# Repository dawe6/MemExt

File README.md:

# MemExt
## Obsah
    • Úvod 
    • Realizace zapojení 
        ◦ Popis zapojení 
        ◦ Instalace modulu 
    • Používání modulu MemExt 
        ◦ Příklady nastavení stránkování 
        ◦ Inicializace stránkování 
        ◦ Postup při programování FLASH 
        ◦ Programování FLASH mimo MZ800 
        ◦ Obsah paměti FLASH 

## Úvod
Modul MemExt umožní používat v MZ800 až 1 MB operační paměti. Obsahuje stránkovací systém, který převádí 16-ti bitovou adresu mikroprocesoru Z80 na 20-ti bitovou adresu paměti. 
      Slovníček pojmů:
    • Logická paměť - to je paměť kterou známe jako fyzickou RAM z MZ800 před instalací MemExt. Má velikost 64kB a může mít adresu 0-FFFFh. 
    • Fyzická paměť - to je celková paměť. Její velikost je 1MB a může mít adresu 0-FFFFFh. Je rozdělená na dvě části 512 kB RAM a 512 kB FLASH. 
    • Stránkovací paměť - je prostředníkem mezi logickou a fyzickou pamětí. Její velikost je pouhých 16 bajtů. 
    • Stránkování - je hlavní činností modulu MemExt. Je to převod 16-ti bitové adresy na 20-ti bitovou. Ve skutečnosti ovšem nejvyšší 4 adresní bity (A12-A15) adresují jednu z 16-ti buněk stránkovací paměti a její 8-mi bitový výstup pak doplní 12 nižších adresních bitů (A0-A11) na 20-ti bitovou adresu. 
    • Stránkovací adresa - má tento tvar "BB:AAA" kde BB /0-FFh/ je obsah stránkovací paměti, "AAA" /0-FFFh/ jsou spodní nestránkované bity adresy. 
    • Stránka - má velikost 4 kB. Logická paměť má 16 stránek, fyzická paměť pak 256 z toho 128 v RAM a 128 ve FLASH. 
    • Mapování - je mapování pamětí VRAM a PROM pomocí I/O portů 0E0h-0E4h. Mapování je nadřazeno stránkování. Pokud přimapujeme část FLASH budu ji označovat jako PROM, protože do mapované FLASH není možný zápis. Pro programování FLASH je nutné použít stránkování. MemExt rozšiřuje vlastnosti mapování PROM na možnost volit ze dvou 16 kB části FLASH přepínačem MZ700/MZ800. 
Nastavení stránkovací paměti se provádí zápisem na I/O port E7h, kde se 8 bitů datové sběrnice zapisuje do buňky určené nejvyššími 4-mi bity 16-ti bitové adresní sběrnice, nastavení tedy musí být provedeno instrukcí OUT (C), r kdy vyšší 4 bity registru B určují adresu ve stránkovací paměti. Zapojení neumožňuje stránkovací paměť programově číst. 

## Popis zapojení
    • Adresní dekodér I/O portu E7h - Je tvořen obvody LS138 a LS10 (3 hradla).
Výstupem je pin 15 obvodu LS138 a nabývá log "0" při zápisu do I/O portu E7h. 
    • Logika módu stránkování / mapování - Sestává pouze z obvodu LS157.
Vstupem S (pin 1 LS157) je signál /CSROM (původní /CS pro paměť PROM). Mux s výstupem Q3 (pin 9) funguje jako invertor signálu /CSROM a jeho aktivita zakazuje stránkovací paměť a generuje signál /CS pro paměť FLASH. Pokud je vstup /CSROM aktivní (log "0") platí:
- signál /ME (memory enabled) u obvodů 7489 je v log "1",
- signál /CS u paměti FLASH je v log "0",
- B12 = A12 (mux s výstupem Q1 pin 4),
- B13 = A13 (mux s výstupem Q4 pin 12),
- B14, B15 = log "0" (výstupy stránkovací paměti v log "1" a invertor),
- B16 = stav přepínače, mód MZ700 = log "1", mód MZ800 = log "0", (mux s výstupem Q2 pin 7),
- B17, B18 = log "1" (výstupy stránkovací paměti v log "1"). 
    • Stránkovací paměť - Je tvořen dvěma obvody 7489, pěti invertory obvodu LS04, osmi odpory 1k (obvod 7489 má na výstupu otevřený kolektor)
Paměť je neaktivní jedině v případě aktivity signálu /CSROM (mód mapování). Jinak paměť neustále generuje podle bitů A12 - A15 adresní sběrnice signály B12 - B19. V případě zápisu do I/O portu E7h je aktivní signál /WE (pin 3) a bity datové sbětnice se zapíší do buňky stránkovací paměti vybrané bity A12 - A15 adresní sběrnice 
    • Logika výběru RAM / FLASH - Sestává z obvodu LS02 (4 hradla) a invertoru obvodu LS04.
Vstupem je signál /CAS, který aktivoval původní paměťové čipy 4164 - nyní vstupuje na piny 6 a 8 obvodu LS02. Druhým rozhodovacím signálem je nejvyšší adresní výstup stránkovací paměti B19 - ten rozhodne zda bude aktivována paměť RAM nebo FLASH. Paměť FLASH může být také aktivovaná signálem /CSROM. 
    • Paměti FLASH/RAM - Obvody 29F040 a 628512.
Tady snad jedině že 628512 nemá uspořádané piny jako 29F040 tak jsou adresní vodiče v zapojení poněkud přeházené, ale vzhledem k tomu že je to RAM tak to snad ani nevadí. 

## Instalace modulu
    • Nejprve je třeba si připravit pomocný datový konektor se sedmi vodiči a připájet je podle obrázku mb.jpg na základní desku. Pořadí vodičů na pomocném konektoru (od zadní části MZ800) je:
A14
/WR
/RD
/IORQ
A15
7/8
/CAS. 
    • Druhým krokem je odstavení stávajících čipů RAM 4164. To je realizováno přerušením signálu CAS. Podle obrázku mb.jpg najděte nad obvodem 8253 čtyři odpory v řadě (na mém obrázku je čtvrtý odpor nahrazen propojkou, kterou jsem tam dal kvůli testování abych nemusel stále pájet). Vypájejte nožičku čtvrtého odporu směřující k obvodu 74LS125 a připojte ji na +5V. 
    • Teď vyndejte z patice paměť PROM a místo ní vložte modul a připojte pomocný datový konektor. 
    • Mužete zkusit co to udělá, když se to zapne. 

## Příklady nastavení stránkování
Ovládání stránkovacího mechanizmu je velice jednoduché tak jen pár příkladů: 
      Ať logickou paměť 2000-2FFF tvoří stránka 00 (první stránka RAM) 
    • LD BC, 20E7 - B=adresa stránkovací paměti 2, C=port stránkování 
    • LD A, 00 - A=stránka 
    • OUT (C), A
Ať logickou paměť 9000-9FFF tvoří stránka 7F (poslední stránka RAM) 
    • LD BC, 90E7 - B=adresa stránkovací paměti 9, C=port stránkování 
    • LD A, 7F - A=stránka 
    • OUT (C), A
Ať logickou paměť 4000-4FFF tvoří stránka 80 (první stránka FLASH) 
    • LD BC, 40E7 - B=adresa stránkovací paměti 4, C=port stránkování 
    • LD A, 80 - A=stránka 
    • OUT (C), A
Ať logickou paměť C000-CFFF tvoří stránka FF (poslední stránka FLASH) 
    • LD BC, C0E7 - B=adresa stránkovací paměti C, C=port stránkování 
    • LD A, FF - A=stránka 
    • OUT (C), A
Představme si, že máme odmapované všechny PROM a SHARP je v módu MZ-800 a chceme pomocí stránkování provést ekvivalent příkazu OUT (E4), A. 
    • LD BC, 00E7 - B=adresa stránkovací paměti 0, C=port stránkování 
    • LD A, 80 - A=stránka 
    • OUT (C), A 
    • LD B, E0 - B=adresa stránkovací paměti E 
    • LD A, 82 - A=stránka (stránka 81 je znakový generátor) 
    • OUT (C), A 
    • LD B, F0 - B=adresa stránkovací paměti F 
    • INC A - A=stránka 83 
    • OUT (C), A 

## Inicializace stránkování
Protože HW inicializace stránkování by byla příliš složitá je nutná úprava BIOSu. Následující program nastaví stránkovací paměť takto: logická paměť 0-FFFh bude mít přimapovanou stránku 00, logická paměť 1000-1FFFh bude mít přimapovanou stránku 01, ..., logická paměť F000-FFFFh bude mít přimapovanou stránku 0F.
0000h
JP 748h
C3 48 07
úprava počátečního skoku
0748h
LD BC, 0E7h
01 E7 00
B=0 adresa stránkovací paměti, C=IO port stránkování
074Bh
LD E, Bh
58
E=0 hodnota stránkovaní
074Ch
OUT (C), E
ED 59
ulož hodnotu pro stránkovaní
074Eh
INC E
1C
zvýšení hodnoty pro stránkovací paměť
074Fh
LD A, B
78
zvýšení adresy stránkovací paměti
0750h
ADD A, 10h
C6 10

0752h
LD B, A
47

0753h
JR NZ, 074Ch
20 F7
smyčka poběží celkem 16x
0755h
JP E800h
C3 00 E8
pokračovat na IPL
## Postup při programování FLASH
Zadání:
1. mám v logické paměti na adrese 2000-2FFF něco co chci dostat do FLASH do stránky A3
2. stránka A3 ve FLASH je buď prázdná, a nebo mě nezajímá co se stane s obsahem stránek A0, A1, A2, A4 - AF
3. mohu si přistránkovat FLASH na adresy 3000-3FFF (program a zásobník je v logické paměti někde jinde)
Přistránkování FLASH
4000h
LD BC, 30E7h
B=30 (logická paměť 3000-3FFF), C=port stránkování
4003h
LD A, 0A3h
A=A3 (stránka FLASH A3)
4005h
OUT (C), A
nastav stránkování
Hlavní smyčka
4007h
LD HL, 2000h
HL=data adresa zdroje
400Ah
LD DE, 3000h
DE=data adresa cíle (programování)
400Dh
LD A, 0F0h
RESET OBVODU FLASH - zápis bajtu F0 kamkoli
400Fh
LD (DE), A

4010h
LD A, (DE)
Čte bajt z FLASH
4011h
CP (HL)
a pokud to není stejné s tím co tam máme dát
skočíme na programování
4012h
JR NZ,401Ch

4014h
INC HL
další adresy
4015h
INC DE

4016h
LD A, H
test jestli to už není vše
4017h
CP 30h

4019h
JR NZ, 4010h

401Bh
RET

Programování bajtu
401Ch
AND (HL)
kontrola zda bajt může být naprogramován:
nelze programovat log "1" na log "0"
pokud nelze musí se sektor paměti FLASH nejprve vymazat
401Dh
CP (HL)

401Eh
JR NZ,403Bh

4020h
LD A, 0AAh
Sekvence programování - krok 1
na adresu ve FLASH xx555 zapiš AA
4022h
LD (3555h), A

4025h
CPL
Sekvence programování - krok 2
na adresu ve FLASH xx2AA zapiš 55
4026h
LD (32AAh), A

4029h
LD A, 0A0h
Sekvence programování - krok 3
na adresu ve FLASH xx555 zapiš A0
402Bh
LD (3555h), A

402Eh
LD A, (HL)
Sekvence programování - krok 4
na správnou adresu zapiš správný bajt
402Fh
LD (DE), A

4030h
LD C, A
bajt dej i do C
4031h
LD A, (DE)
čti bajt z FLASH 
4032h
CP C
pokud jsou tam správná data
konec programování bajtu 
4033h
JR Z, 400Dh

4035h
BIT 5, A
pokud je konec časového limitu
konec programování bajtu 
4037h
JR Z, 400Dh

4039h
JR 4031h
další průchod čtením a testováním 
Mazání sektoru FLASH (!!! pozor maže celý sektor FLASH to je 16 stránek !!!)
403Bh
LD A, 0AAh
Sekvence sektor erase - krok 1
na adresu ve FLASH xx555 zapiš AA
403Dh
LD (3555h), A

4040h
CPL
Sekvence sektor erase - krok 2
na adresu ve FLASH xx2AA zapiš 55
4041h
LD (32AAh), A

4044h
LD A, 80h
Sekvence sektor erase - krok 3
na adresu ve FLASH xx555 zapiš 80
4046h
LD (3555h), A

4049h
LD A, 0AAh
Sekvence sektor erase - krok 4
na adresu ve FLASH xx555 zapiš AA
404Bh
LD (3555h), A

404Eh
CPL
Sekvence sektor erase - krok 5
na adresu ve FLASH xx2AA zapiš 55
404Fh
LD (32AAh), A

4052h
LD A, 30h
Sekvence sektor erase - krok 6
na nějakou adresu ve správném sektoru zapiš 30
4054h
LD (DE), A

4055h
LD B, 0
chvilku počkej
4057h
EX (SP), HL

4058h
DJNZ 4057h

405Ah
LD A, (DE)
a pokud sektor není vymazán čekej dál
405Bh
INC A

405Ch
JR NZ, 4057h

405Eh
JR 4007h
vše znova od začátku
Programování FLASH mimo MZ800
Vzhledem k tomu, že obvod 7489 neguje data jsou na výstupech zapojeny invertory 74LS04, ale výstupů je osm a invertorů jen šest. Proto se neshodují adresy FLASH v MZ800 s adresami v jiném programátoru - nejsou totiž invertovány nejvyšší adresní bity B17 a B18.
Skutečná adresa FLASH
Adresa FLASH v MZ800
Stránkovací adresa
Mapování BIOSu
00000h
60000h
E0:000h
 
10000h
70000h
F0:000h
 
20000h
40000h
C0:000h
 
30000h
50000h
D0:000h
 
40000h
20000h
A0:000h
 
50000h
30000h
B0:000h
 
60000h
00000h
80:000h
mód MZ800 stránky 80h, 81h, 82h a 83h
70000h
10000h
90:000h
mód MZ700 stránky 90h, 91h, 92h a 93h

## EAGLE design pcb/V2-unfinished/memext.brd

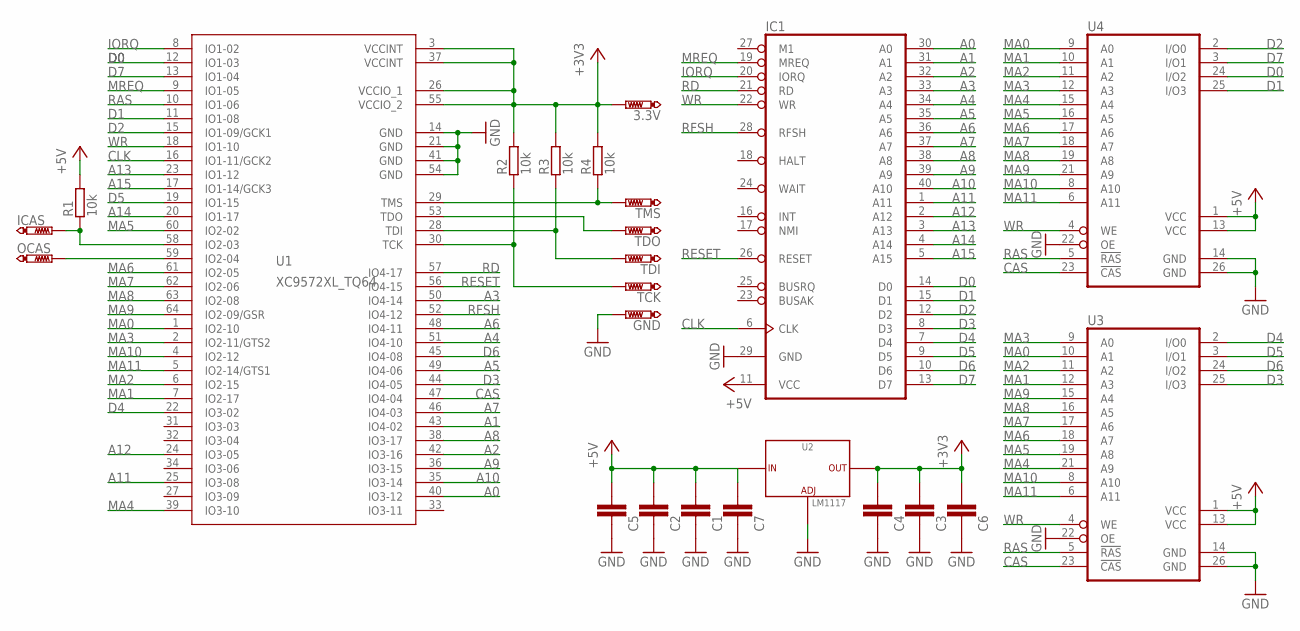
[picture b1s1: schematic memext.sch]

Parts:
3.3V: PTR1TP15SQ; TP15SQ
C1, C2, C3, C4, C5, C6, C7: KONDENZATORYC0603; 0603
GND: PTR1TP15SQ; TP15SQ
IC1: Z80CPU; DIL40
ICAS: PTR1TP15SQ; TP15SQ
OCAS: PTR1TP15SQ; TP15SQ
R1, R2, R3, R4: 10k; 0603
TCK: PTR1TP15SQ; TP15SQ
TDI: PTR1TP15SQ; TP15SQ
TDO: PTR1TP15SQ; TP15SQ
TMS: PTR1TP15SQ; TP15SQ
U1: XC9572XL_TQ64; TQ-64
U2: LM1117; SOT-223
U3, U4: DRAM4X4; SOJ26-24

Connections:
+3V3: 3.3V.TP, C3.2, C4.2, C6.2, R2.2, R3.2, R4.2, U1.3 (VCCINT), U1.26 (VCCIO_1), U1.37 (VCCINT), U1.55 (VCCIO_2), U2.2 (OUT), U2.4 (OUT)
+5V: C1.2, C2.2, C5.2, C7.2, IC1.11 (VCC), R1.2, U2.3 (IN), U3.1 (VCC), U3.13 (VCC), U4.1 (VCC), U4.13 (VCC)
A0: IC1.30 (A0), U1.40 (IO3-12)
A1: IC1.31 (A1), U1.43 (IO4-02)
A2: IC1.32 (A2), U1.42 (IO3-16)
A3: IC1.33 (A3), U1.50 (IO4-14)
A4: IC1.34 (A4), U1.51 (IO4-10)
A5: IC1.35 (A5), U1.49 (IO4-06)
A6: IC1.36 (A6), U1.48 (IO4-11)
A7: IC1.37 (A7), U1.46 (IO4-03)
A8: IC1.38 (A8), U1.38 (IO3-17)
A9: IC1.39 (A9), U1.36 (IO3-15)
A10: IC1.40 (A10), U1.35 (IO3-14)
A11: IC1.1 (A11), U1.25 (IO3-08)
A12: IC1.2 (A12), U1.24 (IO3-05)
A13: IC1.3 (A13), U1.23 (IO1-12)
A14: IC1.4 (A14), U1.20 (IO1-17)
A15: IC1.5 (A15), U1.17 (IO1-14/GCK3)
CAS: U1.47 (IO4-04), U3.23 (!CAS), U4.23 (!CAS)
CLK: IC1.6 (CLK), U1.16 (IO1-11/GCK2)
D0: IC1.14 (D0), U1.12 (IO1-03), U4.24 (I/O2)
D1: IC1.15 (D1), U1.11 (IO1-08), U4.25 (I/O3)
D2: IC1.12 (D2), U1.15 (IO1-09/GCK1), U4.2 (I/O0)
D3: IC1.8 (D3), U1.44 (IO4-05), U3.25 (I/O3)
D4: IC1.7 (D4), U1.22 (IO3-02), U3.2 (I/O0)
D5: IC1.9 (D5), U1.19 (IO1-15), U3.3 (I/O1)
D6: IC1.10 (D6), U1.45 (IO4-08), U3.24 (I/O2)
D7: IC1.13 (D7), U1.13 (IO1-04), U4.3 (I/O1)
GND: C1.1, C2.1, C3.1, C4.1, C5.1, C6.1, C7.1, GND.TP, IC1.29 (GND), U1.14 (GND), U1.21 (GND), U1.41 (GND), U1.54 (GND), U2.1 (ADJ), U3.14 (GND), U3.22 (OE), U3.26 (GND), U4.14 (GND), U4.22 (OE), U4.26 (GND)
IORQ: IC1.20 (IORQ), U1.8 (IO1-02)
MA0: U1.1 (IO2-10), U3.10 (A1), U4.9 (A0)
MA1: U1.7 (IO2-17), U3.12 (A3), U4.10 (A1)
MA2: U1.6 (IO2-15), U3.11 (A2), U4.11 (A2)
MA3: U1.2 (IO2-11/GTS2), U3.9 (A0), U4.12 (A3)
MA4: U1.39 (IO3-10), U3.21 (A9), U4.15 (A4)
MA5: U1.60 (IO2-02), U3.19 (A8), U4.16 (A5)
MA6: U1.61 (IO2-05), U3.18 (A7), U4.17 (A6)
MA7: U1.62 (IO2-06), U3.17 (A6), U4.18 (A7)
MA8: U1.63 (IO2-08), U3.16 (A5), U4.19 (A8)
MA9: U1.64 (IO2-09/GSR), U3.15 (A4), U4.21 (A9)
MA10: U1.4 (IO2-12), U3.8 (A10), U4.8 (A10)
MA11: U1.5 (IO2-14/GTS1), U3.6 (A11), U4.6 (A11)
MREQ: IC1.19 (MREQ), U1.9 (IO1-05)
unnamed: R4.1, TMS.TP, U1.29 (TMS)
unnamed: TDO.TP, U1.53 (TDO)
unnamed: R3.1, TDI.TP, U1.28 (TDI)
unnamed: R2.1, TCK.TP, U1.30 (TCK)
RAS: U1.10 (IO1-06), U3.5 (!RAS), U4.5 (!RAS)
RD: IC1.21 (RD), U1.57 (IO4-17)
RESET: IC1.26 (RESET), U1.56 (IO4-15)
RFSH: IC1.28 (RFSH), U1.52 (IO4-12)
TP1: ICAS.TP, R1.1, U1.58 (IO2-03)
TP2: OCAS.TP, U1.59 (IO2-04)
WR: IC1.22 (WR), U1.18 (IO1-10), U3.4 (WE), U4.4 (WE)

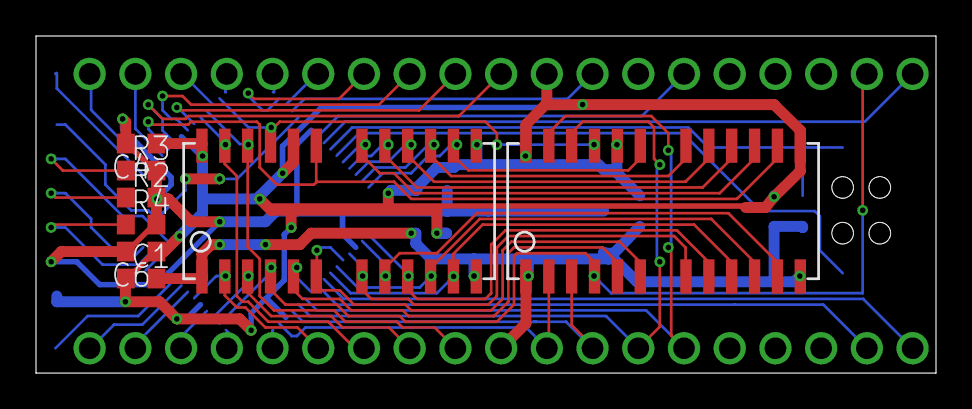
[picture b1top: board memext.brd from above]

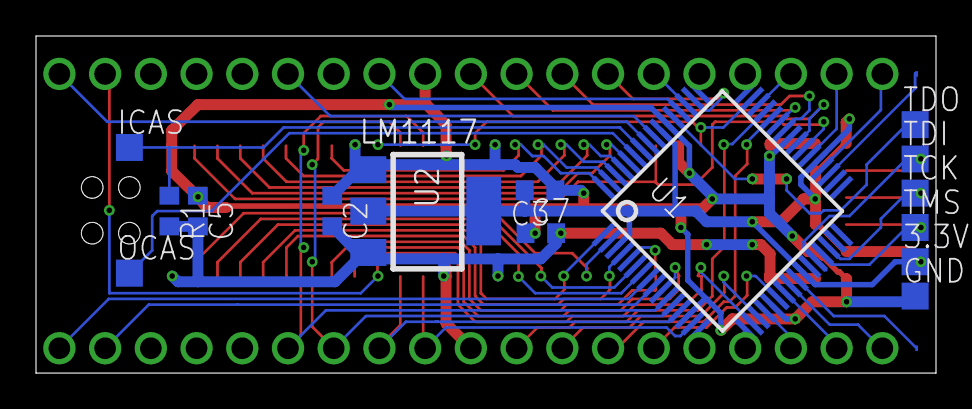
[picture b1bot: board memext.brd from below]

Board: 2 copper layers, 50.0 x 18.7 mm, 24 parts (15 on the bottom side), 54 nets.

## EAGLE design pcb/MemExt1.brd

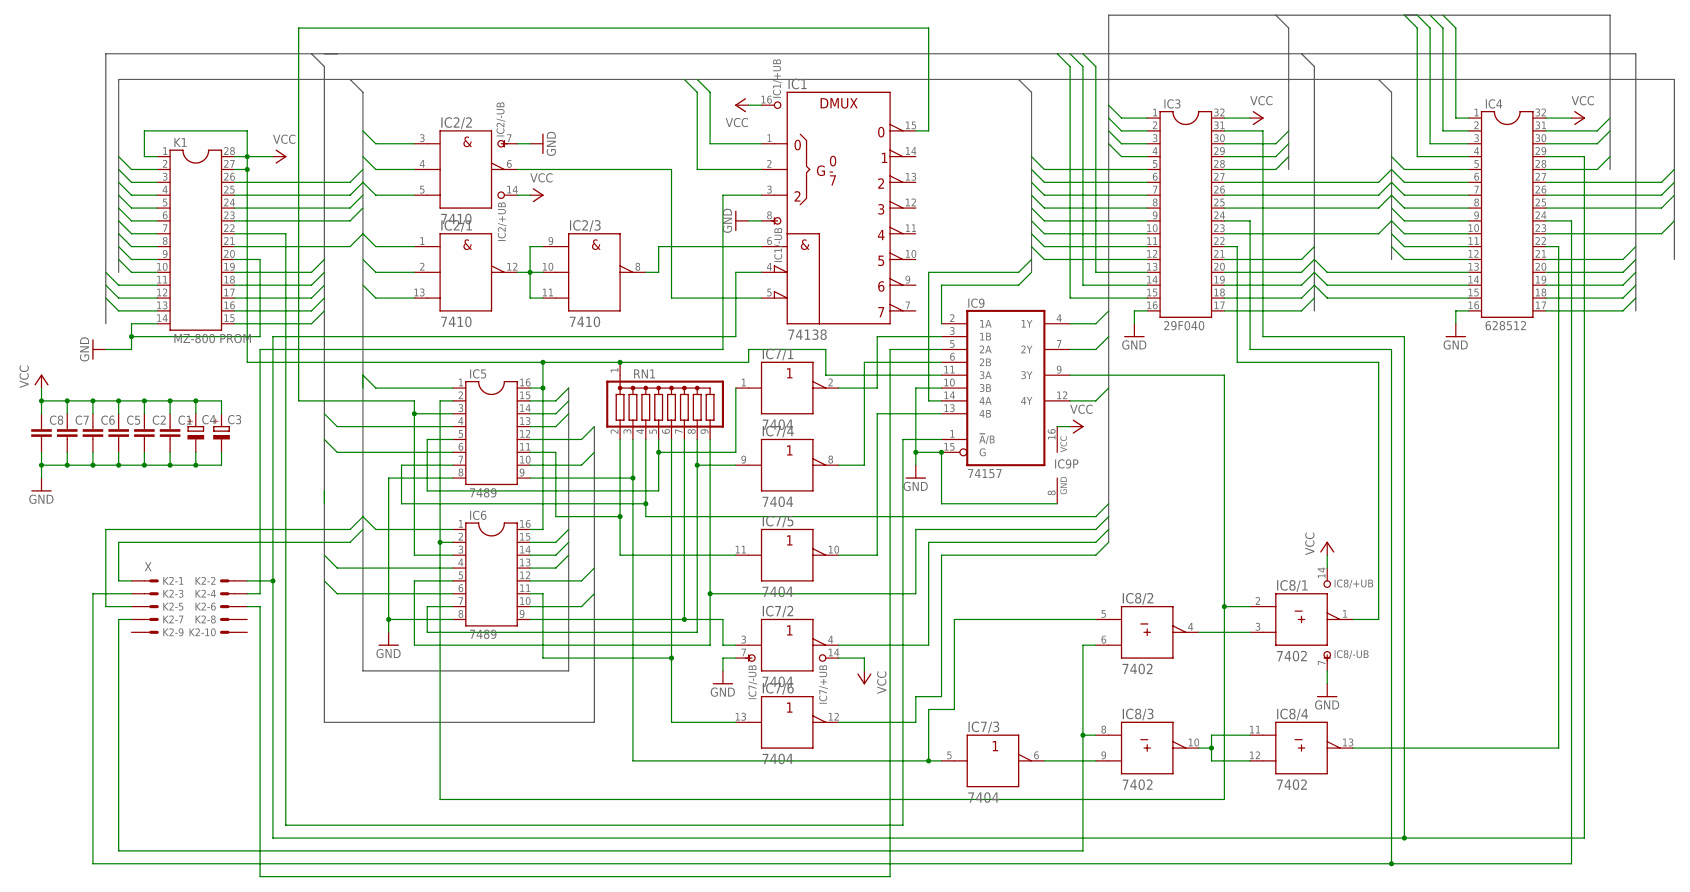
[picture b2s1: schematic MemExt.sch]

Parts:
C1, C2, C5, C6, C7, C8: C-EU050-024X044; C050-024X044
C3, C4: CPOL-EUE1.8-4; E1,8-4
IC1: 74138; DIL16
IC2: 7410; DIL14
IC3: 29F040; DIL32
IC4: 628512; DIL32
IC5, IC6: 7489; DIL16
IC7: 7404; DIL14
IC8: 7402; DIL14
IC9: 74157; DIL16
K1: MZ-800 PROM; DIL28-6
K2: X; 057-010-1
RN1: G08R; SIL9

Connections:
A0: IC2.5 (C), IC3.12, IC4.12, K1.10
A1: IC2.4 (B), IC3.11, IC4.11, K1.9
A2: IC2.3 (A), IC3.10, IC4.10, K1.8
A3: IC1.1 (A), IC3.9, IC4.9, K1.7
A4: IC1.2 (B), IC3.8, IC4.8, K1.6
A5: IC2.2 (B), IC3.7, IC4.7, K1.5
A6: IC2.1 (A), IC3.6, IC4.6, K1.4
A7: IC2.13 (C), IC3.5, IC4.5, K1.3
A8: IC3.27, IC4.27, K1.25
A9: IC3.26, IC4.26, K1.24
A10: IC3.23, IC4.23, K1.21
A11: IC3.25, IC4.25, K1.23
A12: IC5.1, IC6.1, IC9.2 (1A), K1.2
A13: IC5.13, IC6.13, IC9.14 (4A), K1.26
A14: IC5.14, IC6.14, K2.1
A15: IC5.15, IC6.15, K2.5
B12: IC3.4, IC4.4, IC9.4 (1Y)
B13: IC3.28, IC4.28, IC9.12 (4Y)
B14: IC3.29, IC4.30, IC7.4 (Y)
B15: IC3.3, IC4.3, IC7.12 (Y)
B16: IC3.2, IC4.2, IC9.7 (2Y)
B17: IC3.30, IC4.31, IC5.7, RN1.4
B18: IC3.1, IC4.1, IC6.5, RN1.9
D0: IC3.13, IC4.13, IC5.4, K1.11
D1: IC3.14, IC4.14, IC5.12, K1.12
D2: IC3.15, IC4.15, IC6.10, K1.13
D3: IC3.17, IC4.17, IC6.12, K1.15
D4: IC3.18, IC4.18, IC6.6, K1.16
D5: IC3.19, IC4.19, IC5.6, K1.17
D6: IC3.20, IC4.20, IC6.4, K1.18
D7: IC3.21, IC4.21, IC5.10, K1.19
GND: C1.2, C2.2, C3.-, C4.-, C5.2, C6.2, C7.2, C8.2, IC1.8 (-UB), IC2.7 (-UB), IC3.16, IC4.16, IC5.8, IC6.8, IC7.7 (-UB), IC8.7 (-UB), IC9.8 (GND), IC9.10 (3B), IC9.15 (G), K1.14, K1.20
unnamed: IC2.9 (A), IC2.10 (B), IC2.11 (C), IC2.12 (Y)
unnamed: IC6.11, IC7.13 (A), RN1.6
unnamed: IC1.5 (!G2B), IC2.6 (Y)
unnamed: IC1.15 (Y0), IC5.3, IC6.3
unnamed: IC5.2, IC6.2, IC8.2 (A), IC9.9 (3Y)
unnamed: IC9.1 (!A!/B), K1.22
unnamed: IC3.24, IC4.24, K2.3
unnamed: IC8.6 (B), IC8.8 (A), K2.7
unnamed: IC8.3 (B), IC8.4 (Y)
unnamed: IC8.10 (Y), IC8.11 (A), IC8.12 (B)
unnamed: IC4.22, IC8.13 (Y)
unnamed: IC3.22, IC8.1 (Y)
unnamed: IC1.3 (C), K2.4
unnamed: IC9.5 (2A), K2.6
unnamed: IC7.6 (Y), IC8.9 (B)
unnamed: IC6.9, IC7.3 (A), RN1.7
unnamed: IC5.9, IC7.5 (A), IC8.5 (A), RN1.3
unnamed: IC6.7, IC7.9 (A), RN1.8
unnamed: IC1.4 (!G2A), IC3.31, IC4.29, K2.2
unnamed: IC5.5, IC7.1 (A), RN1.5
unnamed: IC5.11, IC7.11 (A), RN1.2
unnamed: IC1.6 (G1), IC2.8 (Y)
unnamed: IC7.2 (Y), IC9.3 (1B)
unnamed: IC7.8 (Y), IC9.6 (2B)
unnamed: IC7.10 (Y), IC9.13 (4B)
VCC: C1.1, C2.1, C3.+, C4.+, C5.1, C6.1, C7.1, C8.1, IC1.16 (+UB), IC2.14 (+UB), IC3.32, IC4.32, IC5.16, IC6.16, IC7.14 (+UB), IC8.14 (+UB), IC9.11 (3A), IC9.16 (VCC), K1.1, K1.27, K1.28, RN1.1

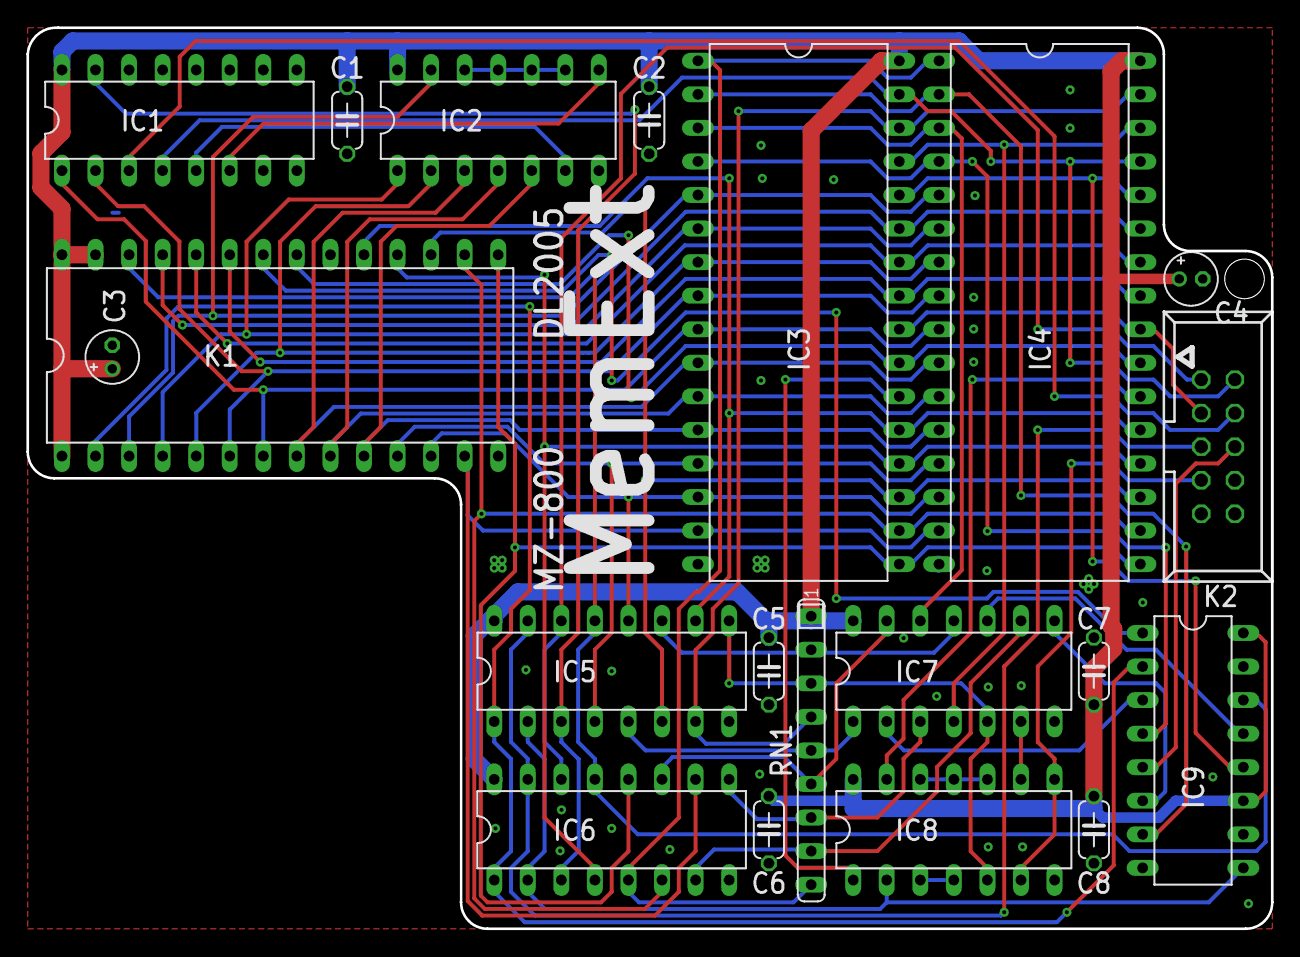
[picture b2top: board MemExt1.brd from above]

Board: 2 copper layers, 94.2 x 68.2 mm, 20 parts (0 on the bottom side), 58 nets.

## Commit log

2023-03-22 Delete MemExt1.brd
    s
2024-11-27 Create LICENSE
